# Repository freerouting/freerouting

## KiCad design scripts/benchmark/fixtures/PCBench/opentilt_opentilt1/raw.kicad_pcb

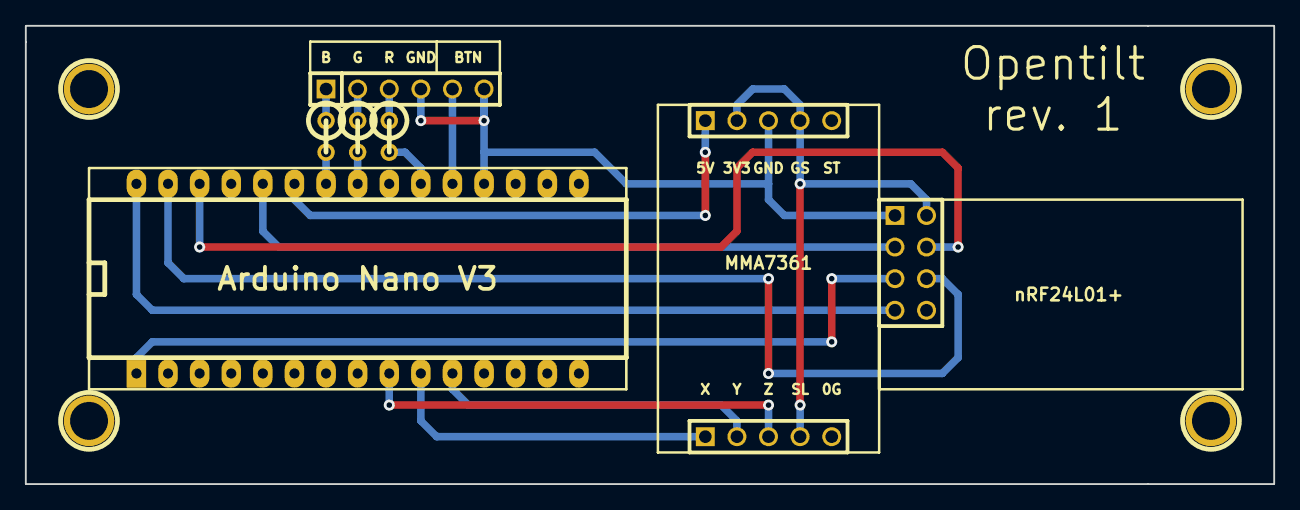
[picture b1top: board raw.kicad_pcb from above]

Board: 2 copper layers, 100.3 x 36.8 mm, 11 parts (0 on the bottom side), 5 nets.

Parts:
1PIN, 1PIN#2, 1PIN#3, 1PIN#4: P***; 1pin
B: R; R1
G: 150; R1
MMA7361: MMA1; PIN_ARRAY_5x1
P2: MMA2; PIN_ARRAY_5x1
P3: CONN_6; PIN_ARRAY-6X1
R: R; R1
nRF24L01+: CONN_4X2; pin_array_4x2

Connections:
GND: MMA7361.3, P3.4, P3.6, nRF24L01+.1
unnamed: P3.3, R.1
unnamed: B.1, P3.1
unnamed: G.1, P3.2
unnamed: MMA7361.2, MMA7361.4, P2.4, nRF24L01+.2

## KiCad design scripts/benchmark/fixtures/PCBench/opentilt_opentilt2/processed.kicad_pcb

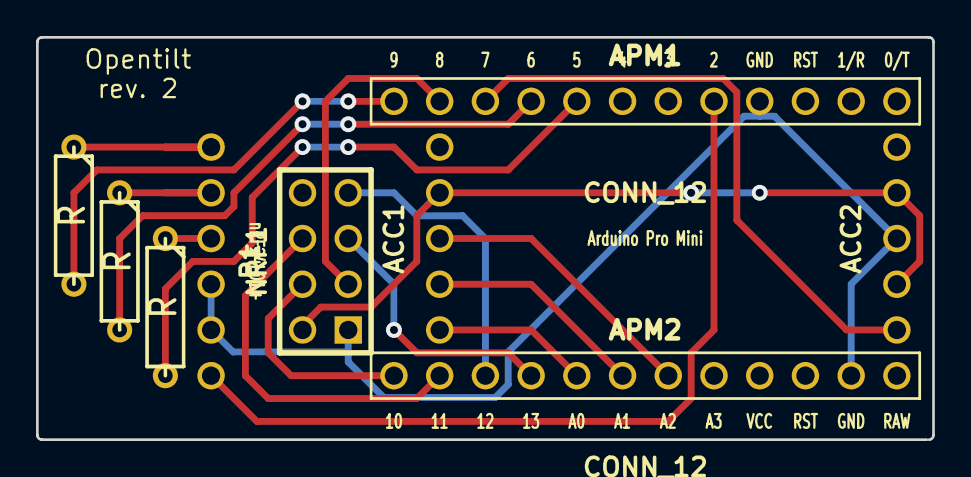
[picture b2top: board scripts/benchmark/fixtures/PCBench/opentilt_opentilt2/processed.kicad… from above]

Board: 2 copper layers, 49.8 x 22.4 mm, 9 parts (0 on the bottom side), 18 nets.

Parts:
ACC1, ACC2: CONN_5; PIN_ARRAY_5x1_B
APM1, APM2: CONN_12; pin_array_12x1
NRF1: CONN_4X2; pin_array_4x2
P1: CONN_6; PIN_ARRAY-6X1_B
RB1: R; R3
RG1: R; R3
RR1: R; R3

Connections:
3V3: ACC1.4, ACC2.2, ACC2.4, NRF1.2
A0: ACC1.1, APM2.8
A1: ACC1.2, APM2.7
A2: ACC1.3, APM2.6
CLK: APM2.9, NRF1.5
D2: APM1.5, P1.6
D5: APM1.8, RR1.2
D6: APM1.9, RG1.2
D7: ACC2.1, APM1.10
D8: APM1.11, NRF1.3
D9: APM1.12, RB1.2
D10: APM2.12, NRF1.4
GND: ACC2.3, APM1.4, APM2.2, NRF1.1, P1.4, P1.5
MISO: APM2.10, NRF1.7
MOSI: APM2.11, NRF1.6
unnamed: P1.3, RR1.1
unnamed: P1.1, RB1.1
unnamed: P1.2, RG1.1

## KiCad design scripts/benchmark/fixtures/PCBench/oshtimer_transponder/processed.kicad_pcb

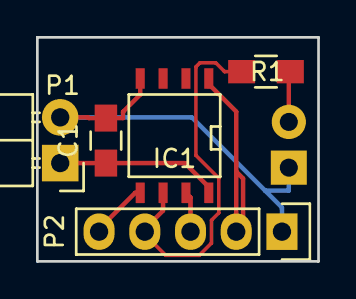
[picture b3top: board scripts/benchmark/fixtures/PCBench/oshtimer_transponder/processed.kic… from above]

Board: 2 copper layers, 15.6 x 12.4 mm, 6 parts (1 on the bottom side), 7 nets.

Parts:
C1: C; C_0805_HandSoldering
D1: IR_LED; LED-5MM
IC1: ATTINY45-S; SOIC-8-N
P1: POWER_CONN; Pin_Header_Angled_1x02
P2: CONN_01X05; Pin_Header_Straight_1x05
R1: R; R_0805_HandSoldering

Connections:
/PROG_MISO: IC1.6, P2.4, R1.1
/PROG_MOSI: IC1.5, P2.5
/PROG_RESET: IC1.1, P2.2
/PROG_SCK: IC1.7, P2.3
GND: C1.2, D1.1, IC1.4, P1.2, P2.1
unnamed: D1.2, R1.2
VCC: C1.1, IC1.8, P1.1
